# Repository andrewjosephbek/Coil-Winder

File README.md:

# Coil Winder

A **low-cost, precision coil winding machine** built from 3D-printed parts and off-the-shelf components, designed for sensing coils, charging coils, solenoids, and similar applications. See detailed system descriptions and methodology in **Design Docs**. 

---

## Highlights
- Winds coils up to **30 mm length × 250 mm diameter**
- Single-piece **3D-printed frame** for tight tolerances and fast assembly
- **Arbor + Eye architecture** for accurate wire placement
- **Stepper-driven arbor** with 3:1 belt reduction for consistent tension
- **Worm-gear driven eye (40:1)** for fine linear positioning
- Custom **4-layer driver PCB** (STM32L432 + DRV8825)
- **FreeRTOS-based firmware** with prioritized motor control and UI tasking

---

## System Overview
- **Arbor Assembly:** Rotates the coil form and maintains wire tension  
- **Eye Assembly:** Precisely guides wire placement across the arbor  
- **Driver Board:** Handles UI, motor drivers, and peripherals  

---

## Tech Stack
STM32L432 · DRV8825 · FreeRTOS · Step/Dir Steppers · 4-layer PCB · 3D Printing

---

## Capabilities
- Tightly packed first-layer winding
- Supports **30 AWG wire**
- Integrated button-based user interface

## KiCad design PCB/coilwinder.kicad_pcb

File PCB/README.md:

# coilwinder PCB

[Replace these texts and sections as needed.  This file should desribe the PCB, and associated information.]

## Background

[Fill this out with general info]

## [Next Section]

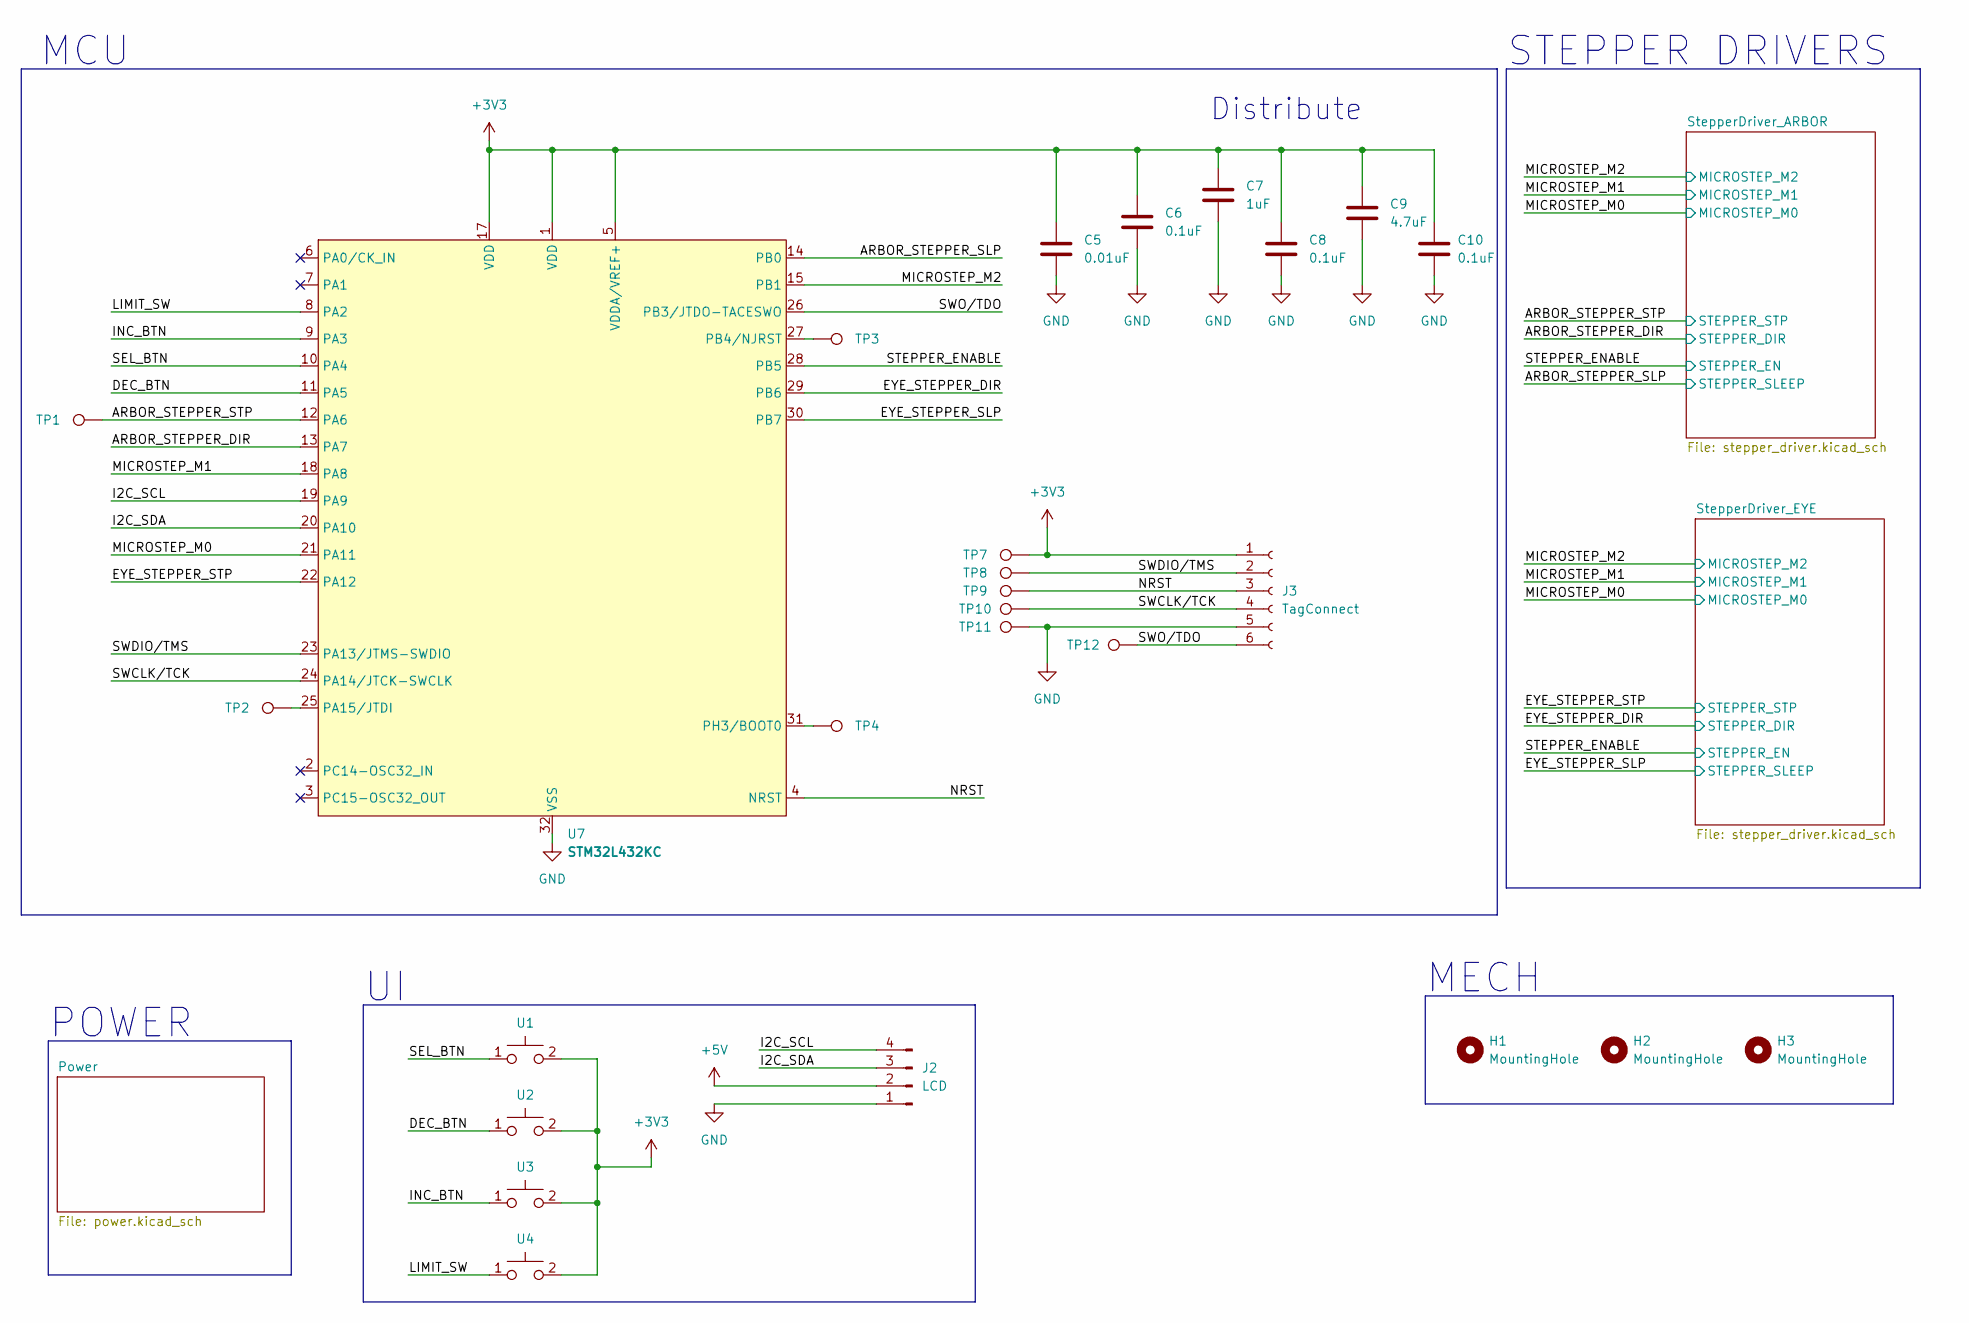
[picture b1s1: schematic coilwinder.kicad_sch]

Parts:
C5: 0.01uF; C_0603_1608Metric_Pad1.08x0.95mm_HandSolder
C6, C8, C10: 0.1uF; C_0603_1608Metric_Pad1.08x0.95mm_HandSolder
C7: 1uF; C_0603_1608Metric_Pad1.08x0.95mm_HandSolder
C9: 4.7uF; C_0603_1608Metric_Pad1.08x0.95mm_HandSolder
H1, H2, H3: MountingHole; MountingHole_2.2mm_M2
J2: LCD; PinHeader_1x04_P2.54mm_Vertical
J3: TagConnect; Tag-Connect_TC2030-IDC-FP_2x03_P1.27mm_Vertical
TP1: TestPoint; TestPoint_Keystone_5000-5004_Miniature
TP2, TP3, TP4, TP7, TP8, TP9, TP10, TP11, TP12: TestPoint; TestPoint_Pad_1.0x1.0mm
U1, U2, U3: TL1150AF070Q Switch
U4: PinHeader_1x02_P2.54mm_Vertical
U7: STM32L432KC; UFQFPN-32-1EP_5x5mm_P0.5mm_EP3.5x3.5mm

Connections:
+3V3: C5.2, C6.2, C7.2, C8.2, C9.2, C10.2, J3.1, TP7.1, U1.2, U2.2, U3.2, U4.2, U7.1 (VDD), U7.5 (VDDA/VREF+), U7.17 (VDD); also elsewhere on the board
+5V: J2.2; also elsewhere on the board
/ARBOR_STEPPER_DIR: U7.13 (PA7); also elsewhere on the board
/ARBOR_STEPPER_SLP: U7.14 (PB0); also elsewhere on the board
/ARBOR_STEPPER_STP: TP1.1, U7.12 (PA6); also elsewhere on the board
/DEC_BTN: U2.1, U7.11 (PA5)
/EYE_STEPPER_DIR: U7.29 (PB6); also elsewhere on the board
/EYE_STEPPER_SLP: U7.30 (PB7); also elsewhere on the board
/EYE_STEPPER_STP: U7.22 (PA12); also elsewhere on the board
/I2C_SCL: J2.4, U7.19 (PA9)
/I2C_SDA: J2.3, U7.20 (PA10)
/INC_BTN: U3.1, U7.9 (PA3)
/LIMIT_SW: U4.1, U7.8 (PA2)
/MICROSTEP_M0: U7.21 (PA11); also elsewhere on the board
/MICROSTEP_M1: U7.18 (PA8); also elsewhere on the board
/MICROSTEP_M2: U7.15 (PB1); also elsewhere on the board
/NRST: J3.3, TP9.1, U7.4 (NRST)
/SEL_BTN: U1.1, U7.10 (PA4)
/STEPPER_ENABLE: U7.28 (PB5); also elsewhere on the board
/SWCLK/TCK: J3.4, TP10.1, U7.24 (PA14/JTCK-SWCLK)
/SWDIO/TMS: J3.2, TP8.1, U7.23 (PA13/JTMS-SWDIO)
/SWO/TDO: J3.6, TP12.1, U7.26 (PB3/JTDO-TACESWO)
GND: C5.1, C6.1, C7.1, C8.1, C9.1, C10.1, J2.1, J3.5, TP11.1, U7.16 (VSS2), U7.32 (VSS), U7.33 (EXP); also elsewhere on the board
unnamed: TP2.1, U7.25 (PA15/JTDI)
unnamed: TP3.1, U7.27 (PB4/NJRST)
unnamed: TP4.1, U7.31 (PH3/BOOT0)

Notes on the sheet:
Distribute
STEPPER DRIVERS
MECH
MCU
POWER

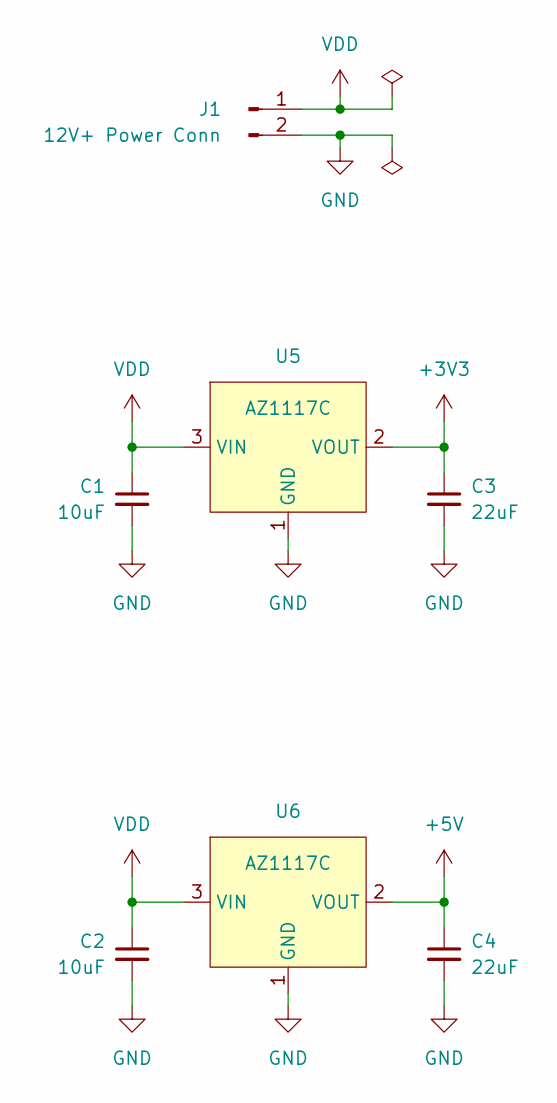
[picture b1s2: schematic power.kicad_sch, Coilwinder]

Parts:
C1, C2: 10uF; C_0603_1608Metric_Pad1.08x0.95mm_HandSolder
C3, C4: 22uF; C_0603_1608Metric_Pad1.08x0.95mm_HandSolder
J1: 12V+ Power Conn; TerminalBlock_bornier-2_P5.08mm
U5, U6: AZ1117C; SOT-223-3_TabPin2

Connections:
+3V3: C3.1, U5.2 (VOUT); also elsewhere on the board
+5V: C4.1, U6.2 (VOUT2); also elsewhere on the board
GND: C1.2, C2.2, C3.2, C4.2, J1.2, U5.1 (GND), U6.1 (GND); also elsewhere on the board
VDD: C1.1, C2.1, J1.1, U5.3 (VIN), U6.3 (VIN); also elsewhere on the board

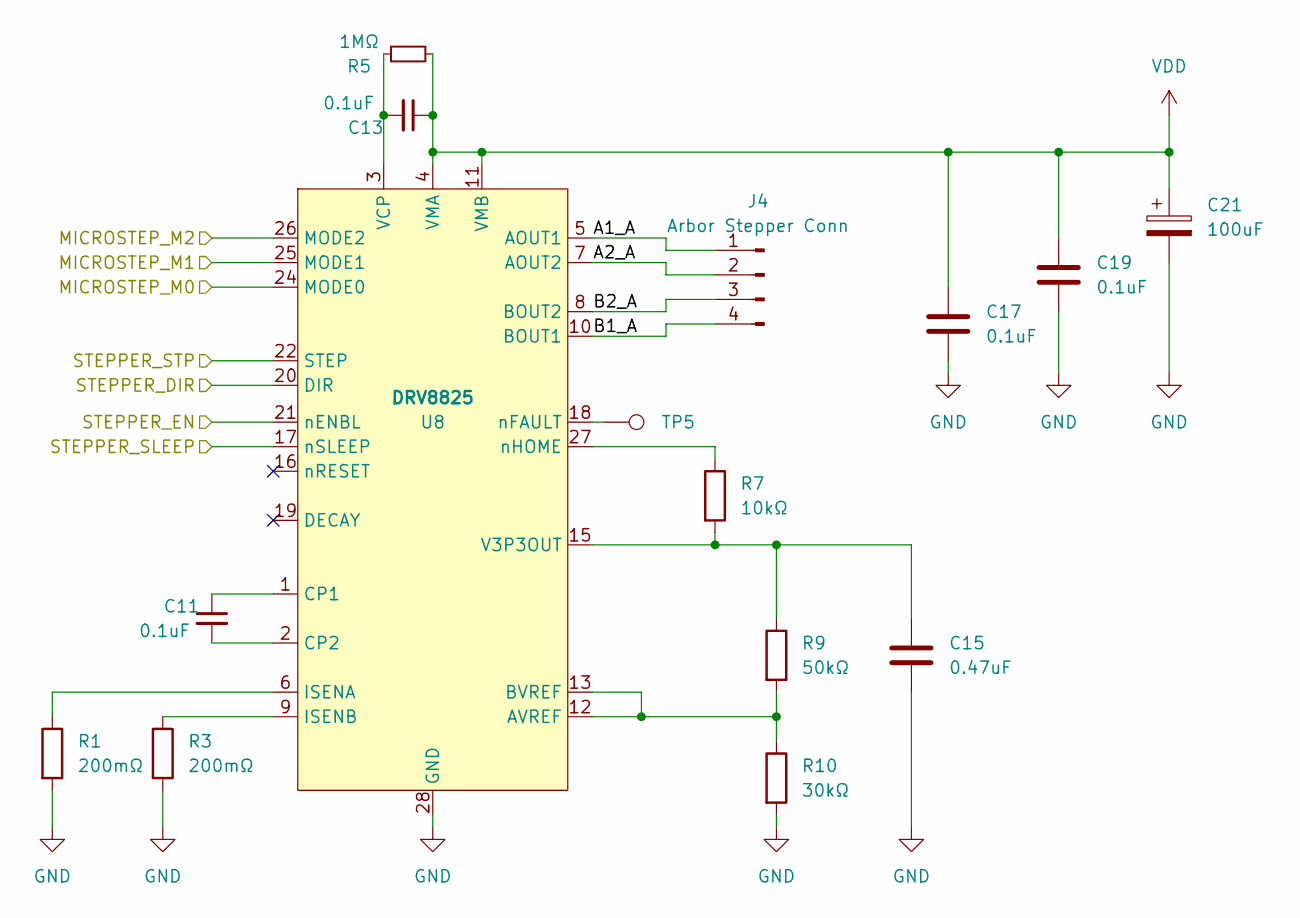
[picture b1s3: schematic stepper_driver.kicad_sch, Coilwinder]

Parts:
C11, C13, C17, C19: 0.1uF; C_0603_1608Metric_Pad1.08x0.95mm_HandSolder
C15: 0.47uF; C_0603_1608Metric_Pad1.08x0.95mm_HandSolder
C21: 100uF; CP_Radial_D5.0mm_P2.00mm
J4: Arbor Stepper Conn; PinHeader_1x04_P2.54mm_Vertical
R1, R3: 200mΩ; C_0603_1608Metric_Pad1.08x0.95mm_HandSolder
R5: 1MΩ; C_0603_1608Metric_Pad1.08x0.95mm_HandSolder
R7: 10kΩ; C_0603_1608Metric_Pad1.08x0.95mm_HandSolder
R9: 50kΩ; C_0603_1608Metric_Pad1.08x0.95mm_HandSolder
R10: 30kΩ; C_0603_1608Metric_Pad1.08x0.95mm_HandSolder
TP5: TestPoint; TestPoint_Pad_1.0x1.0mm
U8: DRV8825

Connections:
/ARBOR_STEPPER_DIR: U8.20 (DIR); also elsewhere on the board
/ARBOR_STEPPER_SLP: U8.17 (nSLEEP); also elsewhere on the board
/ARBOR_STEPPER_STP: U8.22 (STEP); also elsewhere on the board
/MICROSTEP_M0: U8.24 (MODE0); also elsewhere on the board
/MICROSTEP_M1: U8.25 (MODE1); also elsewhere on the board
/MICROSTEP_M2: U8.26 (MODE2); also elsewhere on the board
/STEPPER_ENABLE: U8.21 (nENBL); also elsewhere on the board
/StepperDriver_ARBOR/A1_A: J4.1, U8.5 (AOUT1)
/StepperDriver_ARBOR/A2_A: J4.2, U8.7 (AOUT2)
/StepperDriver_ARBOR/B1_A: J4.4, U8.10 (BOUT1)
/StepperDriver_ARBOR/B2_A: J4.3, U8.8 (BOUT2)
GND: C15.2, C17.1, C19.1, C21.2, R1.2, R3.2, R10.2, U8.14 (GND2), U8.28 (GND), U8.29 (PPAD); also elsewhere on the board
unnamed: R9.2, R10.1, U8.12 (AVREF), U8.13 (BVREF)
unnamed: C11.1, U8.1 (CP1)
unnamed: C11.2, U8.2 (CP2)
unnamed: R1.1, U8.6 (ISENA)
unnamed: R3.1, U8.9 (ISENB)
unnamed: C15.1, R7.2, R9.1, U8.15 (V3P3OUT)
unnamed: C13.2, R5.1, U8.3 (VCP)
unnamed: TP5.1, U8.18 (nFAULT)
unnamed: R7.1, U8.27 (nHOME)
VDD: C13.1, C17.2, C19.2, C21.1, R5.2, U8.4 (VMA), U8.11 (VMB); also elsewhere on the board

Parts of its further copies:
C12, C14, C18, C20: 0.1uF; C_0603_1608Metric_Pad1.08x0.95mm_HandSolder
C16: 0.47uF; C_0603_1608Metric_Pad1.08x0.95mm_HandSolder
C22: 100uF; CP_Radial_D5.0mm_P2.00mm
J5: Arbor Stepper Conn; PinHeader_1x04_P2.54mm_Vertical
R2, R4: 200mΩ; C_0603_1608Metric_Pad1.08x0.95mm_HandSolder
R6: 1MΩ; C_0603_1608Metric_Pad1.08x0.95mm_HandSolder
R8: 10kΩ; C_0603_1608Metric_Pad1.08x0.95mm_HandSolder
R11: 50kΩ; C_0603_1608Metric_Pad1.08x0.95mm_HandSolder
R12: 30kΩ; C_0603_1608Metric_Pad1.08x0.95mm_HandSolder
TP6: TestPoint; TestPoint_Pad_1.0x1.0mm

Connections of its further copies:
/StepperDriver_EYE/A1_A: J5.1; also elsewhere on the board
/StepperDriver_EYE/A2_A: J5.2; also elsewhere on the board
/StepperDriver_EYE/B1_A: J5.4; also elsewhere on the board
/StepperDriver_EYE/B2_A: J5.3; also elsewhere on the board
GND: C16.2, C18.1, C20.1, C22.2, R2.2, R4.2, R12.2; also elsewhere on the board
unnamed 43: R11.2, R12.1; also elsewhere on the board
unnamed 44: C12.1; also elsewhere on the board
unnamed 45: C12.2; also elsewhere on the board
unnamed 46: R2.1; also elsewhere on the board
unnamed 47: R4.1; also elsewhere on the board
unnamed 48: C16.1, R8.2, R11.1; also elsewhere on the board
unnamed 49: C14.2, R6.1; also elsewhere on the board
unnamed 50: TP6.1; also elsewhere on the board
unnamed 51: R8.1; also elsewhere on the board
VDD: C14.1, C18.2, C20.2, C22.1, R6.2; also elsewhere on the board

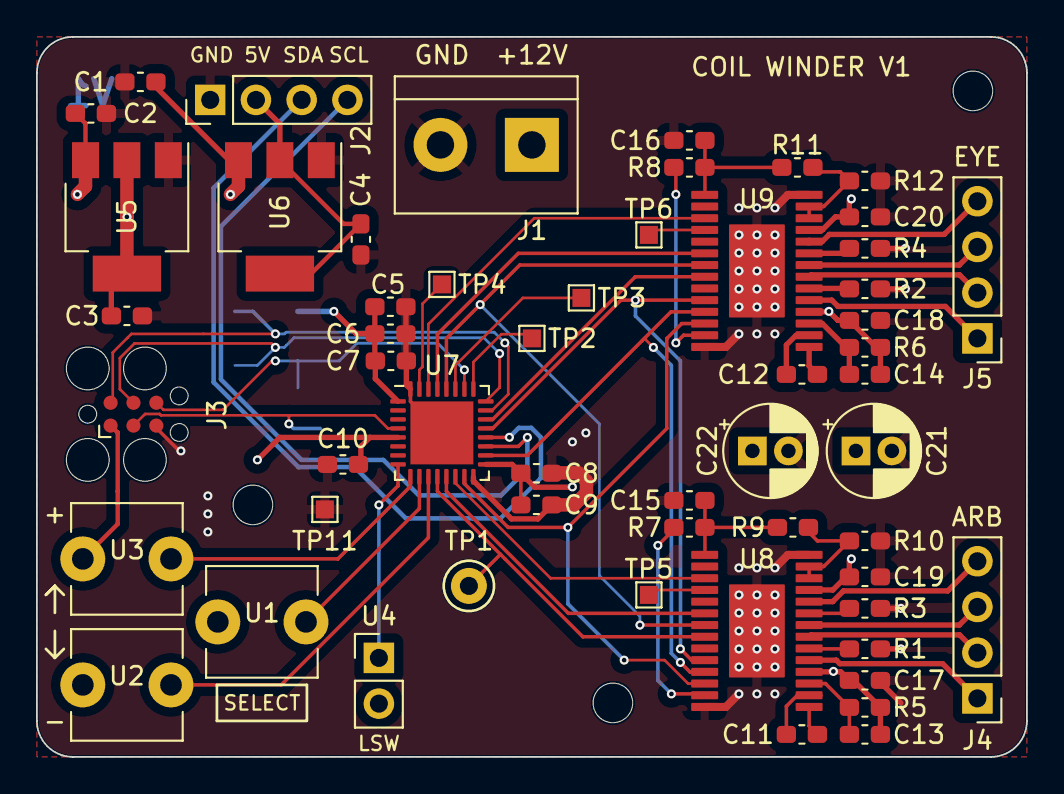
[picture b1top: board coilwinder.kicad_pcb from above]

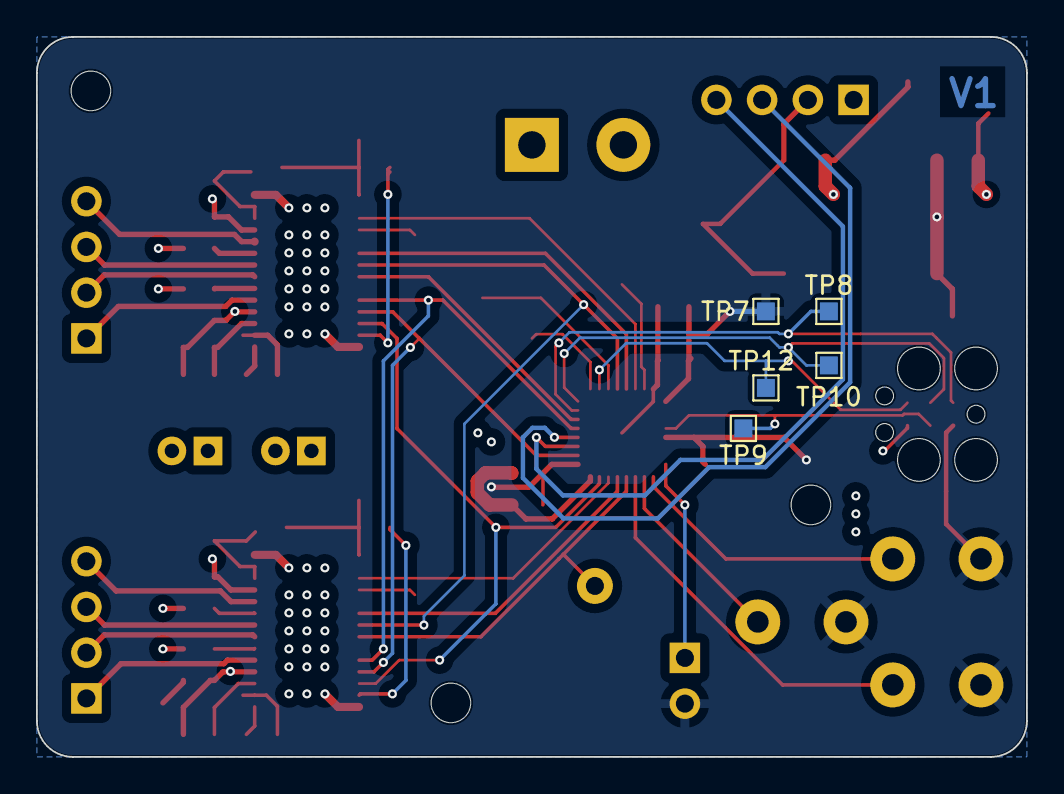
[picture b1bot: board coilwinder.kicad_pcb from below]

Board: 4 copper layers, 55.0 x 40.0 mm, 63 parts (5 on the bottom side), 53 nets.

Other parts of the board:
U9: HTSSOP (28) 9.70 mm × 6.40 mm; DRV8825

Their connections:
/EYE_STEPPER_DIR: U9.20 (DIR); also elsewhere on the board
/EYE_STEPPER_SLP: U9.17 (nSLEEP); also elsewhere on the board
/EYE_STEPPER_STP: U9.22 (STEP); also elsewhere on the board
/MICROSTEP_M0: U9.24 (MODE0); also elsewhere on the board
/MICROSTEP_M1: U9.25 (MODE1); also elsewhere on the board
/MICROSTEP_M2: U9.26 (MODE2); also elsewhere on the board
/STEPPER_ENABLE: U9.21 (nENBL); also elsewhere on the board
/StepperDriver_EYE/A1_A: U9.5 (AOUT1); also elsewhere on the board
/StepperDriver_EYE/A2_A: U9.7 (AOUT2); also elsewhere on the board
/StepperDriver_EYE/B1_A: U9.10 (BOUT1); also elsewhere on the board
/StepperDriver_EYE/B2_A: U9.8 (BOUT2); also elsewhere on the board
GND: U9.14 (GND2), U9.28 (GND), U9.29 (PPAD); also elsewhere on the board
unnamed 43: U9.12 (AVREF), U9.13 (BVREF); also elsewhere on the board
unnamed 44: U9.1 (CP1); also elsewhere on the board
unnamed 45: U9.2 (CP2); also elsewhere on the board
unnamed 46: U9.6 (ISENA); also elsewhere on the board
unnamed 47: U9.9 (ISENB); also elsewhere on the board
unnamed 48: U9.15 (V3P3OUT); also elsewhere on the board
unnamed 49: U9.3 (VCP); also elsewhere on the board
unnamed 50: U9.18 (nFAULT); also elsewhere on the board
unnamed 51: U9.27 (nHOME); also elsewhere on the board
VDD: U9.4 (VMA), U9.11 (VMB); also elsewhere on the board

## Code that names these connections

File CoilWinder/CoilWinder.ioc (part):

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Mcu.Name=STM32L432K(B-C)Ux
Mcu.Package=UFQFPN32
Mcu.UserName=STM32L432KCUx
PA10.Mode=I2C
PA10.Signal=I2C1_SDA
PA11.GPIOParameters=GPIO_PuPd,GPIO_Label
PA11.GPIO_Label=MICROSTEP_M0
PA11.GPIO_PuPd=GPIO_PULLDOWN
PA11.Signal=GPIO_Output
PA12.GPIOParameters=GPIO_Speed,GPIO_PuPd,GPIO_Label
PA12.GPIO_Label=STEPPER_B_STP
PA12.GPIO_PuPd=GPIO_PULLDOWN
PA12.GPIO_Speed=GPIO_SPEED_FREQ_HIGH
PA12.Signal=GPIO_Output
PA2.GPIOParameters=GPIO_PuPd,GPIO_Label
PA2.GPIO_Label=LIMIT_SW
PA2.GPIO_PuPd=GPIO_PULLDOWN
PA2.Signal=GPIO_Input
PA3.GPIOParameters=GPIO_PuPd,GPIO_Label
PA3.GPIO_Label=INC_BTN
PA3.GPIO_PuPd=GPIO_PULLDOWN
PA3.Signal=GPIO_Input
PA4.GPIOParameters=GPIO_PuPd,GPIO_Label
PA4.GPIO_Label=SEL_BTN
PA4.GPIO_PuPd=GPIO_PULLDOWN
PA4.Signal=GPIO_Input
PA5.GPIOParameters=GPIO_PuPd,GPIO_Label
PA5.GPIO_Label=DEC_BTN
PA5.GPIO_PuPd=GPIO_PULLDOWN
PA5.Signal=GPIO_Input
PA6.GPIOParameters=GPIO_Speed,GPIO_PuPd,GPIO_Label
PA6.GPIO_Label=STEPPER_ARBOR_STP
PA6.GPIO_PuPd=GPIO_PULLDOWN
PA6.GPIO_Speed=GPIO_SPEED_FREQ_HIGH
PA6.Signal=GPIO_Output
PA7.GPIOParameters=GPIO_PuPd,GPIO_Label
PA7.GPIO_Label=STEPPER_A_DIR
PA7.GPIO_PuPd=GPIO_PULLDOWN
PA7.Signal=GPIO_Output
PA8.GPIOParameters=GPIO_PuPd,GPIO_Label
PA8.GPIO_Label=MICROSTEP_M1
PA8.GPIO_PuPd=GPIO_PULLDOWN
PA8.Signal=GPIO_Output
PA9.Mode=I2C
PA9.Signal=I2C1_SCL
PB0.GPIOParameters=GPIO_PuPd,GPIO_Label
PB0.GPIO_Label=STEPPER_A_SLP
PB0.GPIO_PuPd=GPIO_PULLDOWN
PB0.Signal=GPIO_Output
PB1.GPIOParameters=GPIO_PuPd,GPIO_Label
PB1.GPIO_Label=MICROSTEP_M2
PB1.GPIO_PuPd=GPIO_PULLDOWN
PB1.Signal=GPIO_Output
PB5.GPIOParameters=GPIO_PuPd,GPIO_Label
PB5.GPIO_Label=STEPPER_ENABLE
PB5.GPIO_PuPd=GPIO_PULLDOWN
PB5.Signal=GPIO_Output
PB6.GPIOParameters=GPIO_PuPd,GPIO_Label
PB6.GPIO_Label=STEPPER_B_DIR
PB6.GPIO_PuPd=GPIO_PULLDOWN
PB6.Signal=GPIO_Output
PB7.GPIOParameters=GPIO_PuPd,GPIO_Label
PB7.GPIO_Label=STEPPER_B_SLP
PB7.GPIO_PuPd=GPIO_PULLDOWN
PB7.Signal=GPIO_Output
RCC.HSE_VALUE=8000000
RCC.SYSCLKFreq_VALUE=80000000
RCC.SYSCLKSource=RCC_SYSCLKSOURCE_PLLCLK
board=custom

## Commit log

2026-01-12 Moved selected files to here
    portfolio
